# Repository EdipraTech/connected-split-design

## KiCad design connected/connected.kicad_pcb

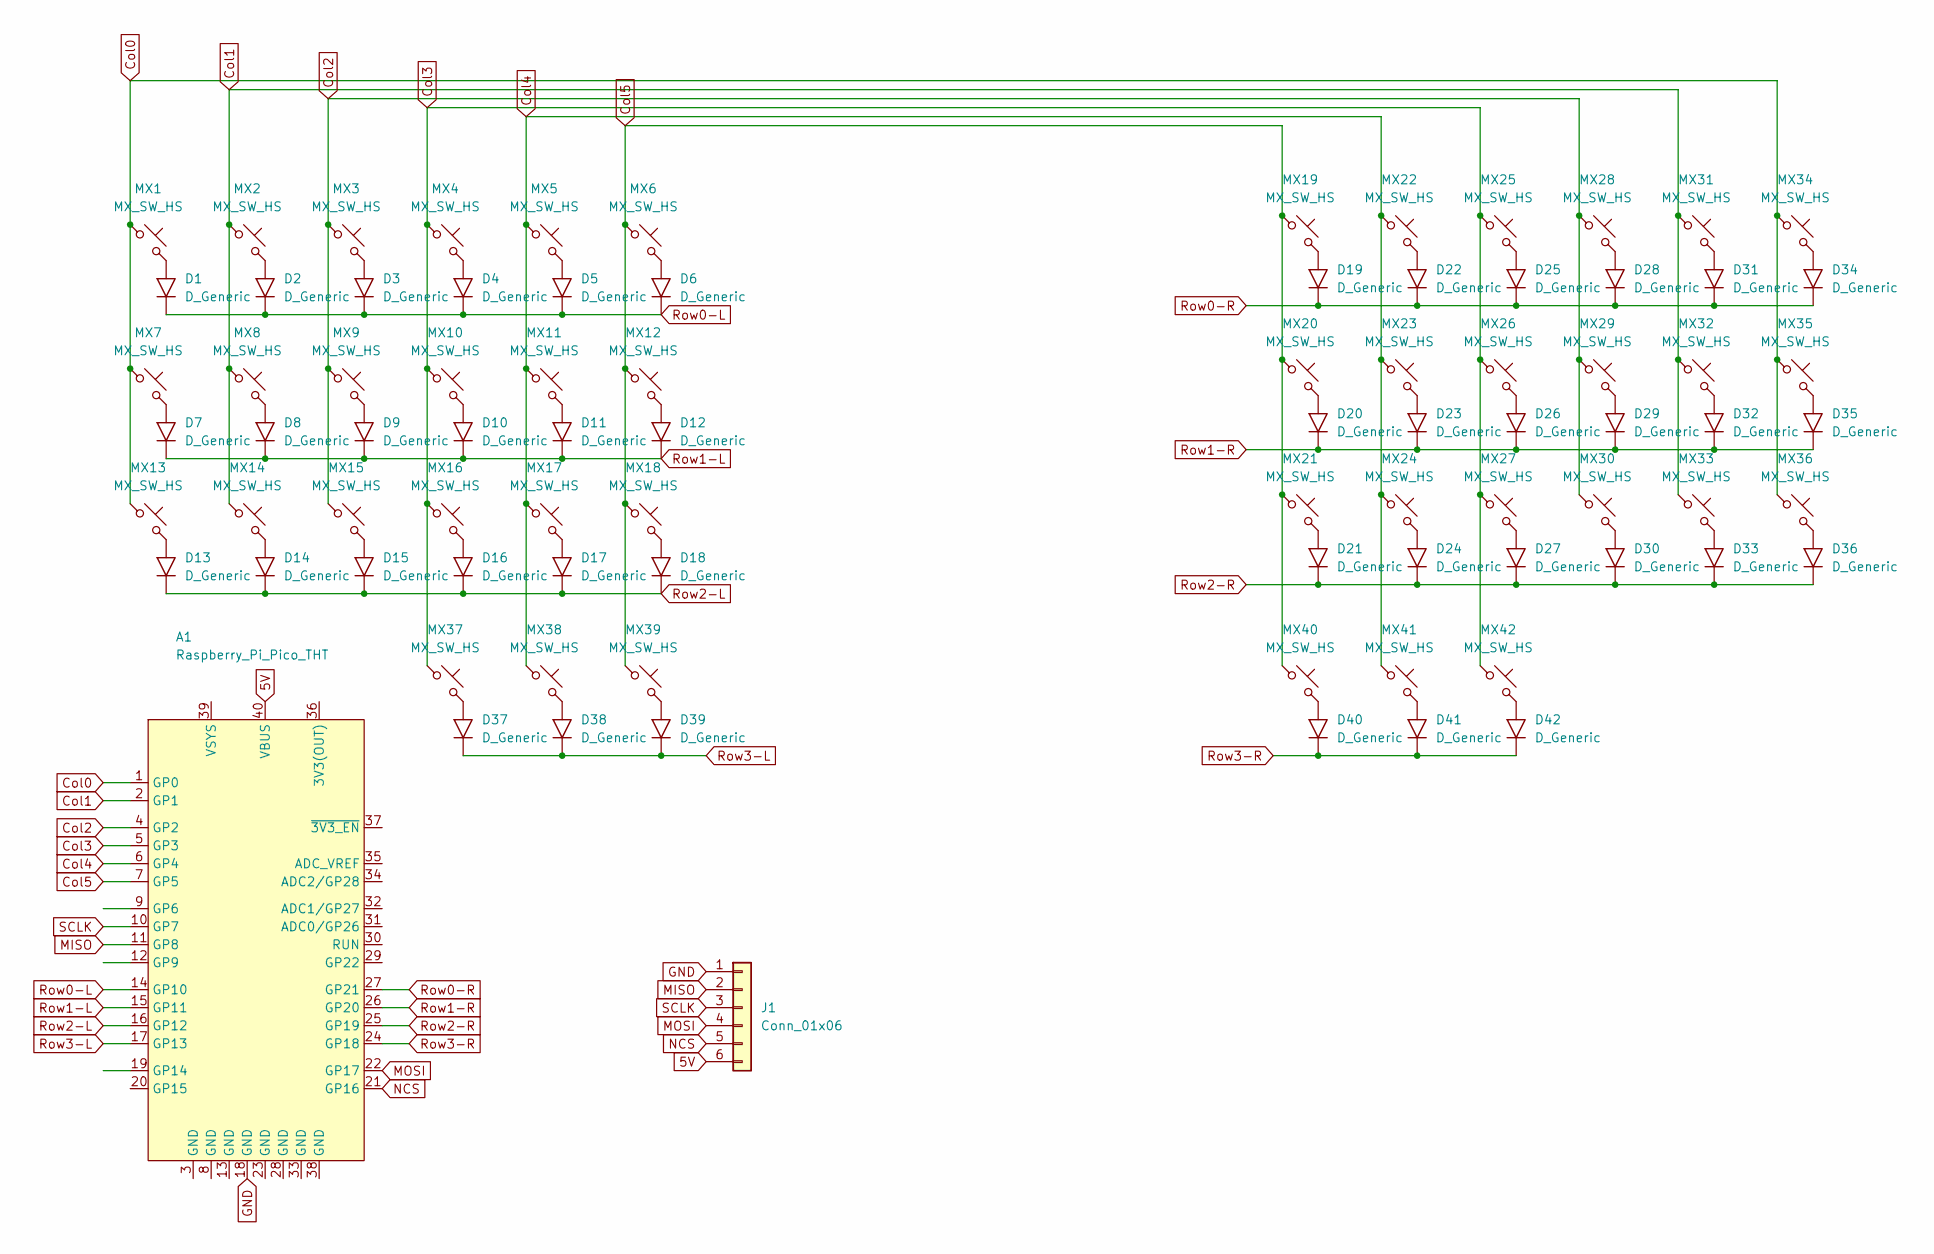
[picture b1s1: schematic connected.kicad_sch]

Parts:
A1: Raspberry_Pi_Pico_THT; raspberry_pi_pico_THT
D1, D2, D3, D4, D5, D6, D7, D8, D9, D10, D11, D12, D13, D14, D15, D16, D17, D18, D19, D20, D21, D22, D23, D24, D25, D26, D27, D28, D29, D30, D31, D32, D33, D34, D35, D36, D37, D38, D39, D40, D41, D42: D_Generic; D_DO-41_P7.62mm_Horizontal
J1: Conn_01x06; Header-6-Pin-ZigZag
MX1, MX2, MX3, MX4, MX5, MX6, MX7, MX8, MX9, MX10, MX11, MX12, MX13, MX14, MX15, MX16, MX17, MX18, MX19, MX20, MX21, MX22, MX23, MX24, MX25, MX26, MX27, MX28, MX29, MX30, MX31, MX32, MX33, MX34, MX35, MX36, MX37, MX38, MX39, MX40, MX41, MX42: MX_SW_HS; SW_Cherry_MX_PCB_1.00u

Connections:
5V: A1.40 (VBUS), J1.6
Col0: A1.1 (GP0), MX1.1, MX7.1, MX13.1, MX34.1, MX35.1, MX36.1
Col1: A1.2 (GP1), MX2.1, MX8.1, MX14.1, MX31.1, MX32.1, MX33.1
Col2: A1.4 (GP2), MX3.1, MX9.1, MX15.1, MX28.1, MX29.1, MX30.1
Col3: A1.5 (GP3), MX4.1, MX10.1, MX16.1, MX25.1, MX26.1, MX27.1, MX37.1, MX42.1
Col4: A1.6 (GP4), MX5.1, MX11.1, MX17.1, MX22.1, MX23.1, MX24.1, MX38.1, MX41.1
Col5: A1.7 (GP5), MX6.1, MX12.1, MX18.1, MX19.1, MX20.1, MX21.1, MX39.1, MX40.1
GND: A1.18 (GND), J1.1
MISO: A1.11 (GP8), J1.2
MOSI: A1.22 (GP17), J1.4
NCS: A1.21 (GP16), J1.5
unnamed: D1.2 (A), MX1.2
unnamed: D2.2 (A), MX2.2
unnamed: D3.2 (A), MX3.2
unnamed: D4.2 (A), MX4.2
unnamed: D5.2 (A), MX5.2
unnamed: D6.2 (A), MX6.2
unnamed: D7.2 (A), MX7.2
unnamed: D8.2 (A), MX8.2
unnamed: D9.2 (A), MX9.2
unnamed: D10.2 (A), MX10.2
unnamed: D11.2 (A), MX11.2
unnamed: D12.2 (A), MX12.2
unnamed: D13.2 (A), MX13.2
unnamed: D14.2 (A), MX14.2
unnamed: D15.2 (A), MX15.2
unnamed: D16.2 (A), MX16.2
unnamed: D17.2 (A), MX17.2
unnamed: D18.2 (A), MX18.2
unnamed: D19.2 (A), MX19.2
unnamed: D20.2 (A), MX20.2
unnamed: D21.2 (A), MX21.2
unnamed: D22.2 (A), MX22.2
unnamed: D23.2 (A), MX23.2
unnamed: D24.2 (A), MX24.2
unnamed: D25.2 (A), MX25.2
unnamed: D26.2 (A), MX26.2
unnamed: D27.2 (A), MX27.2
unnamed: D28.2 (A), MX28.2
unnamed: D29.2 (A), MX29.2
unnamed: D30.2 (A), MX30.2
unnamed: D31.2 (A), MX31.2
unnamed: D32.2 (A), MX32.2
unnamed: D33.2 (A), MX33.2
unnamed: D34.2 (A), MX34.2
unnamed: D35.2 (A), MX35.2
unnamed: D36.2 (A), MX36.2
unnamed: D37.2 (A), MX37.2
unnamed: D38.2 (A), MX38.2
unnamed: D39.2 (A), MX39.2
unnamed: D40.2 (A), MX40.2
unnamed: D41.2 (A), MX41.2
unnamed: D42.2 (A), MX42.2
Row0-L: A1.14 (GP10), D1.1 (K), D2.1 (K), D3.1 (K), D4.1 (K), D5.1 (K), D6.1 (K)
Row0-R: A1.27 (GP21), D19.1 (K), D22.1 (K), D25.1 (K), D28.1 (K), D31.1 (K), D34.1 (K)
Row1-L: A1.15 (GP11), D7.1 (K), D8.1 (K), D9.1 (K), D10.1 (K), D11.1 (K), D12.1 (K)
Row1-R: A1.26 (GP20), D20.1 (K), D23.1 (K), D26.1 (K), D29.1 (K), D32.1 (K), D35.1 (K)
Row2-L: A1.16 (GP12), D13.1 (K), D14.1 (K), D15.1 (K), D16.1 (K), D17.1 (K), D18.1 (K)
Row2-R: A1.25 (GP19), D21.1 (K), D24.1 (K), D27.1 (K), D30.1 (K), D33.1 (K), D36.1 (K)
Row3-L: A1.17 (GP13), D37.1 (K), D38.1 (K), D39.1 (K)
Row3-R: A1.24 (GP18), D40.1 (K), D41.1 (K), D42.1 (K)
SCLK: A1.10 (GP7), J1.3

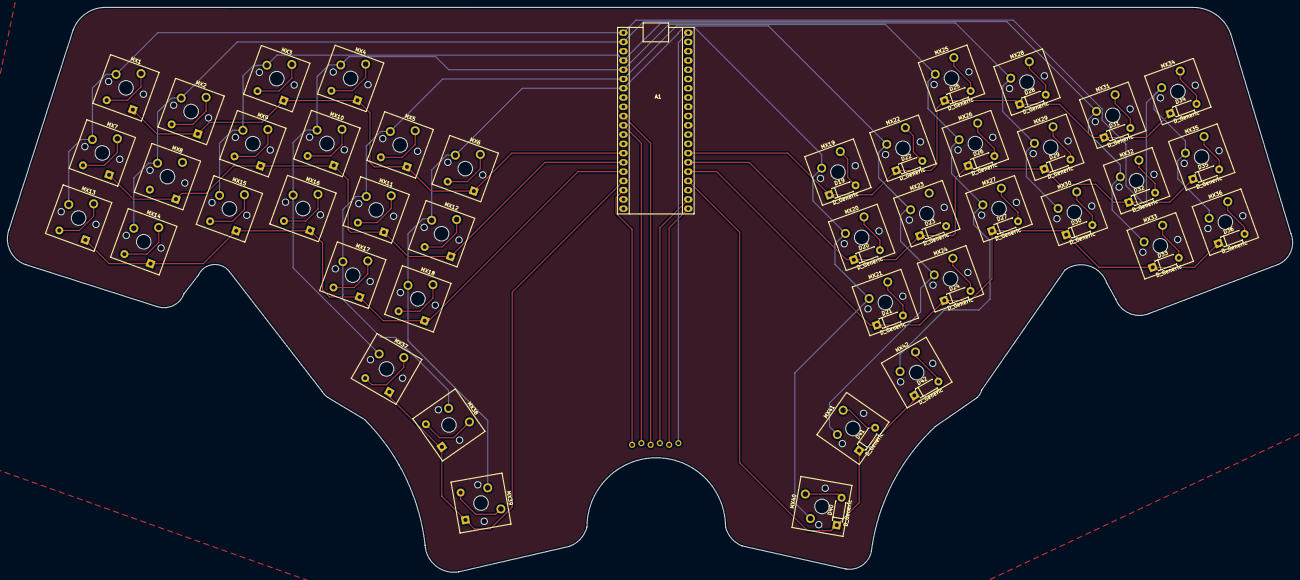
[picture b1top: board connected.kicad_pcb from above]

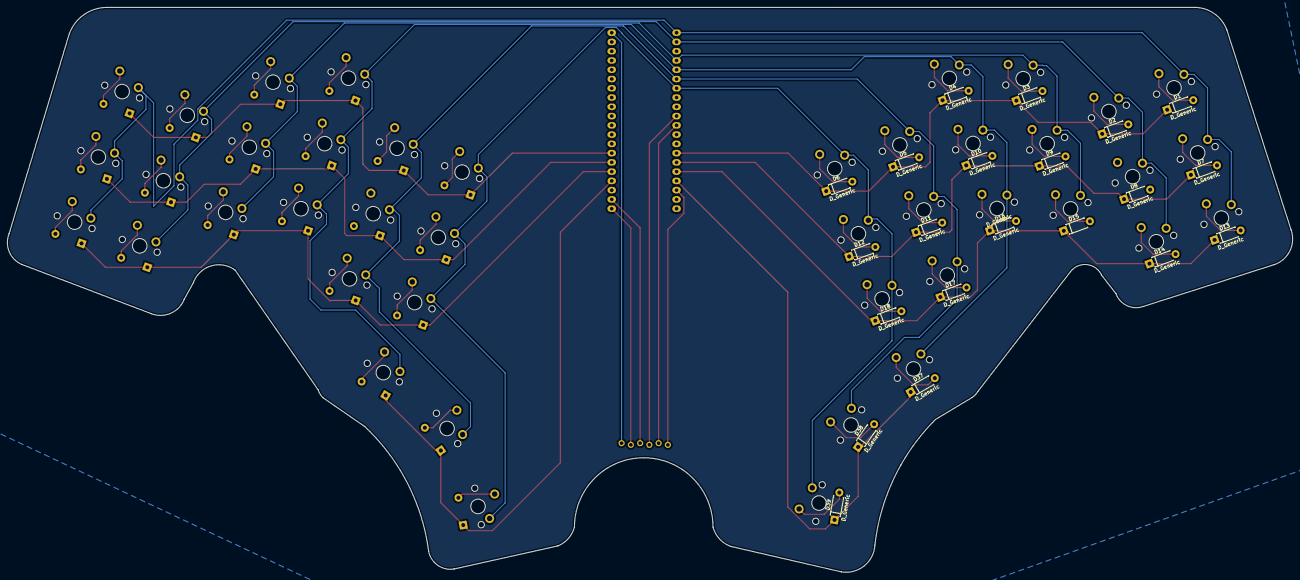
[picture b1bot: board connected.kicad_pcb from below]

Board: 2 copper layers, 352.4 x 154.9 mm, 86 parts (21 on the bottom side), 62 nets.

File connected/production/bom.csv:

Designator,Footprint,Quantity,Value,LCSC Part #
A1,raspberry_pi_pico_THT,1,Raspberry_Pi_Pico_THT,
"D1, D10, D11, D12, D13, D14, D15, D16, D17, D18, D19, D2, D20, D21, D22, D23, D24, D25, D26, D27, D28, D29, D3, D30, D31, D32, D33, D34, D35, D36, D37, D38, D39, D4, D40, D41, D42, D5, D6, D7, D8, D9",D_DO-41_P7.62mm_Horizontal,42,D_Generic,
J1,Header-6-Pin-ZigZag,1,Conn_01x06,
"MX1, MX10, MX11, MX12, MX13, MX14, MX15, MX16, MX17, MX18, MX19, MX2, MX20, MX21, MX22, MX23, MX24, MX25, MX26, MX27, MX28, MX29, MX3, MX30, MX31, MX32, MX33, MX34, MX35, MX36, MX37, MX38, MX39, MX4, MX40, MX41, MX42, MX5, MX6, MX7, MX8, MX9",SW_Cherry_MX_PCB_1.00u,42,MX_SW_HS,

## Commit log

2024-05-08 connected-split-design upload
